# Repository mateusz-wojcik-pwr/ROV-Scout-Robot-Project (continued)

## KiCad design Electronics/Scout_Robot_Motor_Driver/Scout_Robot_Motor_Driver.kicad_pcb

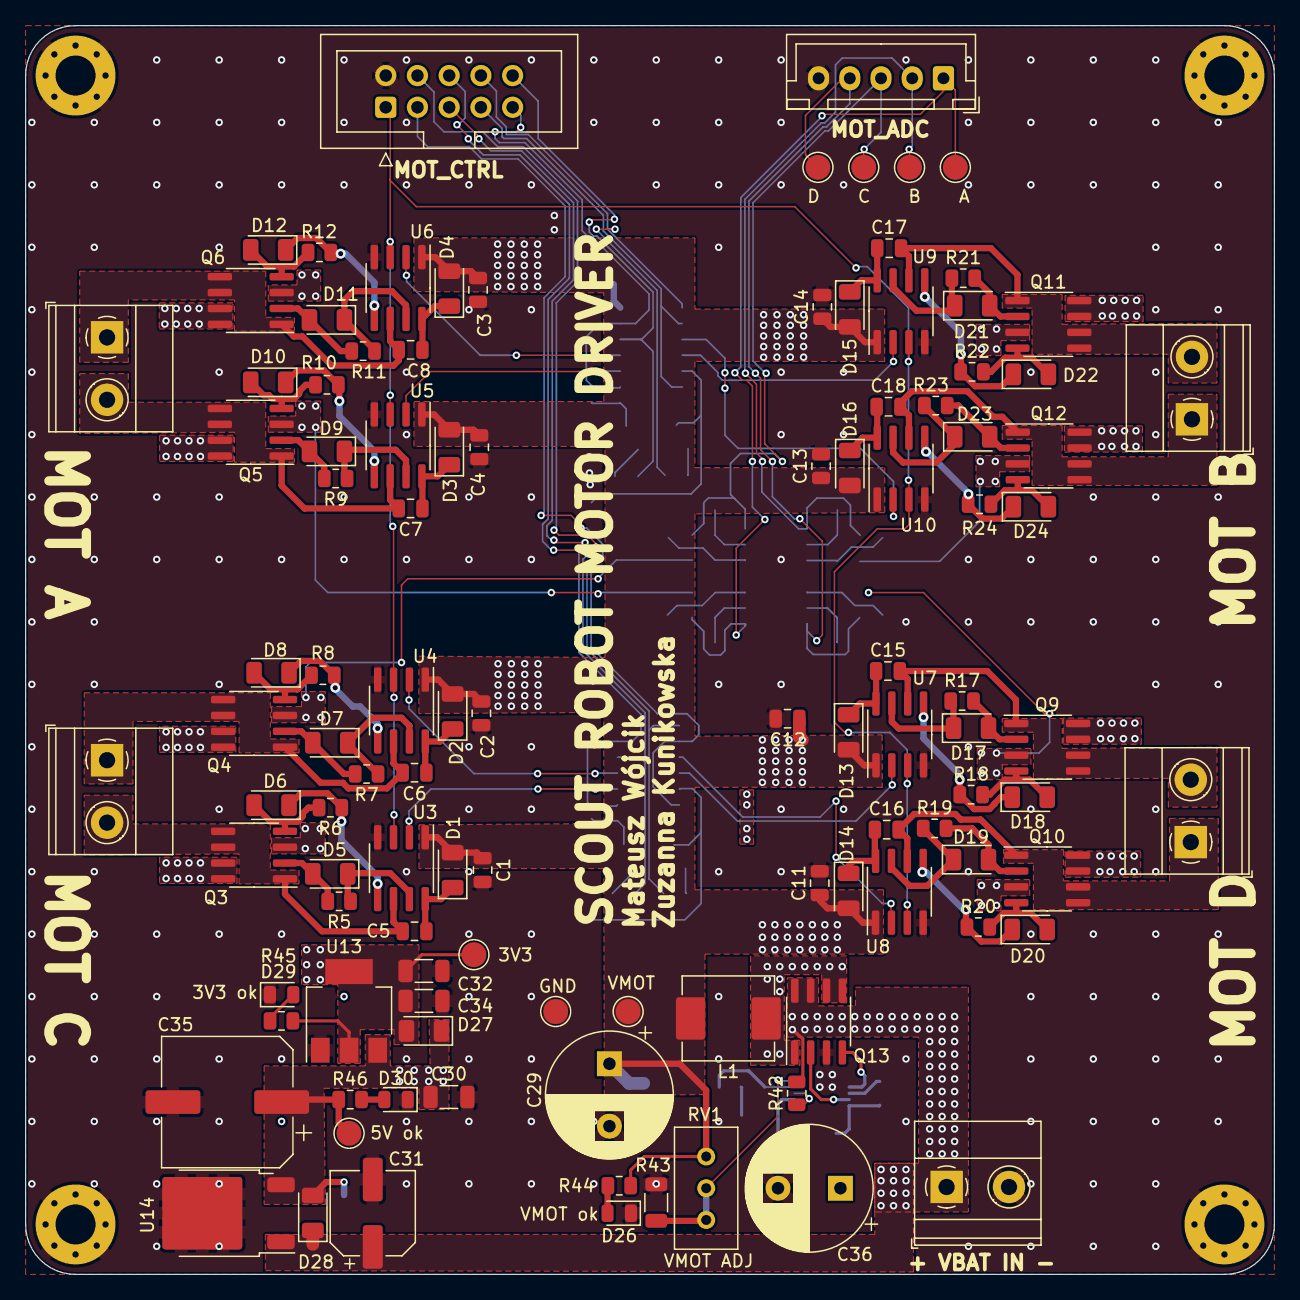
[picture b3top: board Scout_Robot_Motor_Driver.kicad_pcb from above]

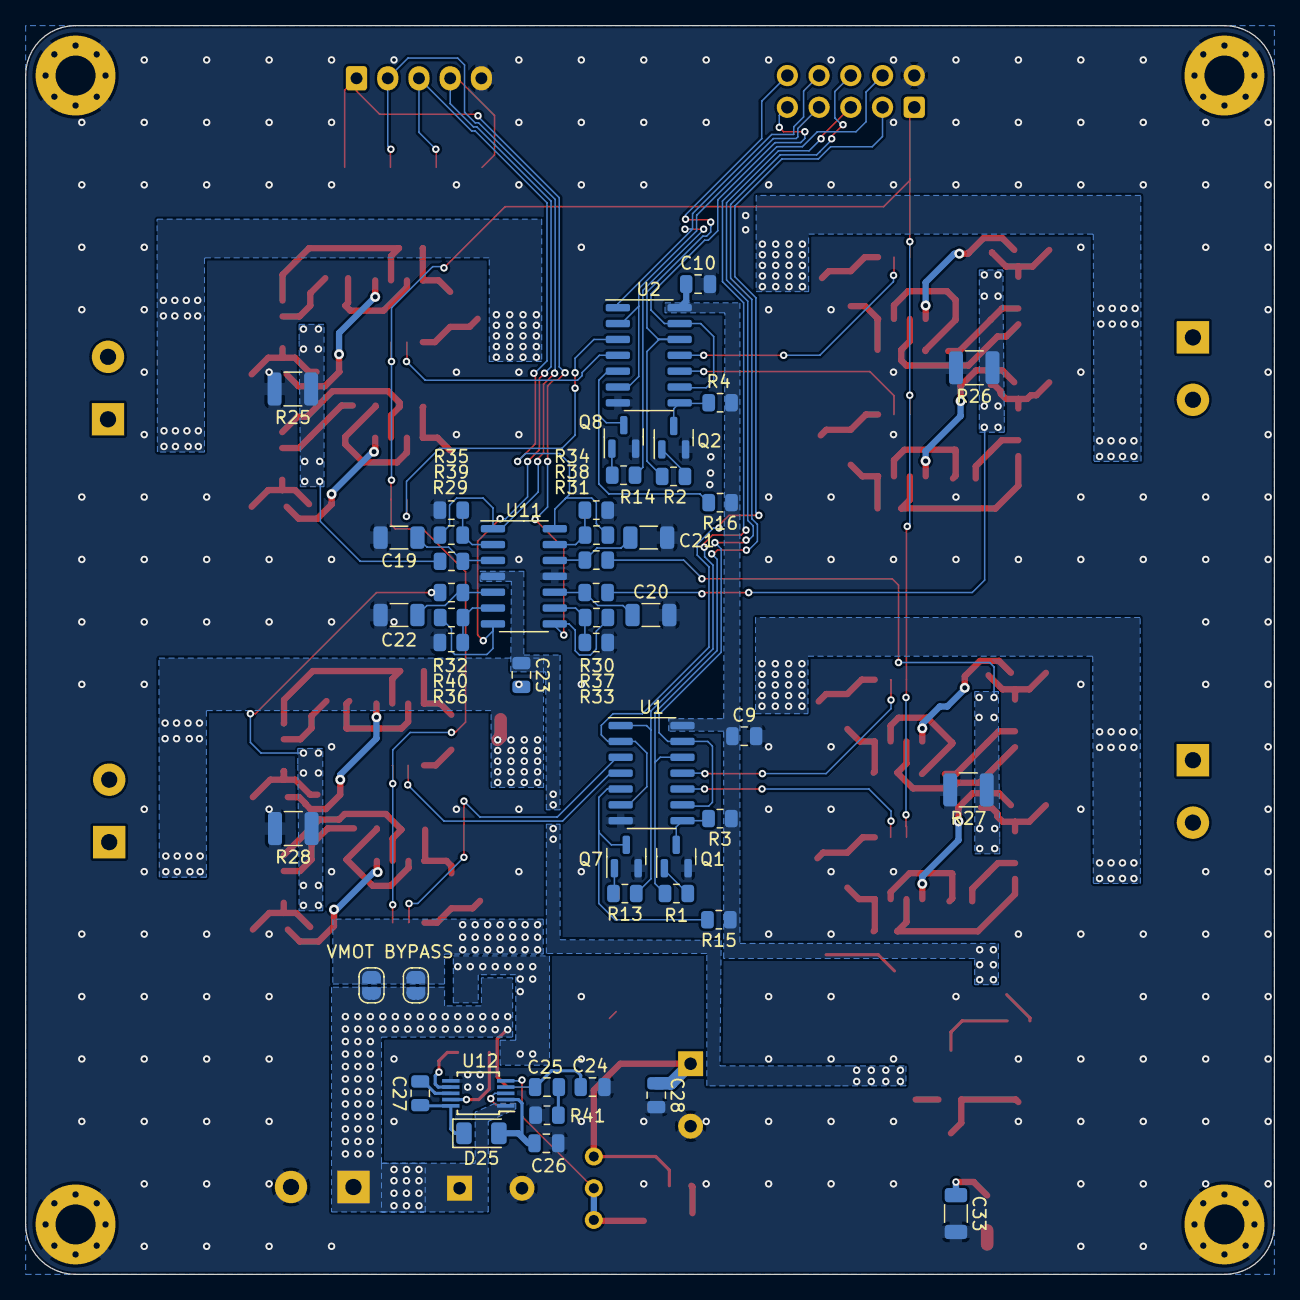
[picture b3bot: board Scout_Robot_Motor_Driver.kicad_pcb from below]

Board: 2 copper layers, 100.0 x 100.0 mm, 162 parts (49 on the bottom side), 107 nets.

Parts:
C1, C2, C3, C4, C5, C6, C7, C8, C9, C10, C11, C12, C13, C14, C15, C16, C17, C18, C23, C25, C26, C27, C28: 100n; C_0805_2012Metric
C19, C20, C21, C22, C30, C32, C33, C34: 1u; C_1206_3216Metric
C24: 100p; C_0805_2012Metric
C29, C36: 470u/25V; CP_Radial_D10.0mm_P5.00mm
C31: 47u/35V; CP_Elec_6.3x5.8
C35: 1m/10V; CP_Elec_10x7.9
D1, D2, D3, D4, D5, D6, D7, D8, D9, D10, D11, D12, D13, D14, D15, D16, D17, D18, D19, D20, D21, D22, D23, D24, D25, D27, D28: D; D_1206_3216Metric
D26: V_MOT_OK; LED_0805_2012Metric
D29: 3V3_OK; LED_0805_2012Metric
D30: 5V_ok; LED_0805_2012Metric
H1, H2, H3, H4: MH; MountingHole_3.2mm_M3_Pad_Via
J1: MOT_A; TerminalBlock_Phoenix_MKDS-1,5-2_1x02_P5.00mm_Horizontal
J2: MOT_B; TerminalBlock_Phoenix_MKDS-1,5-2_1x02_P5.00mm_Horizontal
J3: MOT_C; TerminalBlock_Phoenix_MKDS-1,5-2_1x02_P5.00mm_Horizontal
J4: MOT_D; TerminalBlock_Phoenix_MKDS-1,5-2_1x02_P5.00mm_Horizontal
J5: MOTOR_CONTROL; IDC-Header_2x05_P2.54mm_Vertical
J6: VCC_IN; TerminalBlock_Phoenix_MKDS-1,5-2_1x02_P5.00mm_Horizontal
J7: ADC_CURR_CONN; JST_XH_B5B-XH-A_1x05_P2.50mm_Vertical
JP1, JP2: VMOT_BYPASS; SolderJumper-2_P1.3mm_Open_RoundedPad1.0x1.5mm
L1: 2u2/8A; FERROCORE_HP0630
Q1, Q2, Q7, Q8: Q_NPN_BEC; SOT-23
Q3, Q4, Q5, Q6, Q9, Q10, Q11, Q12, Q13: YJSD12N03A; SOIC-8_3.9x4.9mm_P1.27mm
R1, R2, R13, R14: 22k; R_0805_2012Metric
R3, R4, R15, R16, R44: 1k; R_0805_2012Metric
R5, R6, R7, R8, R9, R10, R11, R12, R17, R18, R19, R20, R21, R22, R23, R24: 10R; R_0805_2012Metric
R25, R26, R27, R28: 50m; R_1210_3225Metric
R29, R30, R31, R32, R33, R34, R35, R36, R41: 4k7; R_0805_2012Metric
R37, R38, R39, R40: 47k; R_0805_2012Metric
R42, R46: 680R; R_0805_2012Metric
R43: 1k5; R_1206_3216Metric
R45: 220R; R_0805_2012Metric
RV1: 22k; Potentiometer_Bourns_3296W_Vertical
TP1, TP3: MOT_A_CURR_TP; TestPoint_Pad_D2.0mm
TP2: MOT_D_CURR_TP; TestPoint_Pad_D2.0mm
TP4: MOT_B_CURR_TP; TestPoint_Pad_D2.0mm
TP5: VD_TP; TestPoint_Pad_D2.0mm
TP6: GND_TP; TestPoint_Pad_D2.0mm
TP7: 3V3_TP; TestPoint_Pad_D2.0mm
TP8: 5V_TP; TestPoint_Pad_D2.0mm
U1, U2: 4081; SOIC-14_3.9x8.7mm_P1.27mm
U3, U4, U5, U6, U7, U8, U9, U10: IR2104; SOIC-8_3.9x4.9mm_P1.27mm
U11: LM324; SOIC-14_3.9x8.7mm_P1.27mm
U12: MIC2168; MSOP-10_3x3mm_P0.5mm
U13: AP1117-33; SOT-223-3_TabPin2
U14: L7805; TO-252-2

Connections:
+3V3: C9.1, C10.1, C32.1, C34.1, D27.2 (A), R3.1, R4.1, R15.1, R16.1, R45.1, TP7.1, U1.14 (VDD), U2.14 (VDD), U13.2 (VO)
+5V: C23.1, C30.1, C33.1, C35.1, D27.1 (K), D28.2 (A), R46.1, TP8.1, U11.4 (V+), U13.3 (VI), U14.3 (OUT)
/H_Bridges/MOT_A_1: C7.2, J1.2, Q5.1 (S1), Q5.5 (D2), Q5.6 (D2), U5.6 (VS)
/H_Bridges/MOT_A_2: C8.2, J1.1, Q6.1 (S1), Q6.5 (D2), Q6.6 (D2), U6.6 (VS)
/H_Bridges/MOT_A_GND: Q5.3 (S2), Q6.3 (S2), R26.1, R30.2
/H_Bridges/MOT_B_1: C17.2, J2.2, Q11.1 (S1), Q11.5 (D2), Q11.6 (D2), U9.6 (VS)
/H_Bridges/MOT_B_2: C18.2, J2.1, Q12.1 (S1), Q12.5 (D2), Q12.6 (D2), U10.6 (VS)
/H_Bridges/MOT_B_GND: Q11.3 (S2), Q12.3 (S2), R25.1, R29.2
/H_Bridges/MOT_C_1: C5.2, J3.2, Q3.1 (S1), Q3.5 (D2), Q3.6 (D2), U3.6 (VS)
/H_Bridges/MOT_C_2: C6.2, J3.1, Q4.1 (S1), Q4.5 (D2), Q4.6 (D2), U4.6 (VS)
/H_Bridges/MOT_C_GND: Q3.3 (S2), Q4.3 (S2), R27.1, R31.2
/H_Bridges/MOT_D_1: C15.2, J4.2, Q9.1 (S1), Q9.5 (D2), Q9.6 (D2), U7.6 (VS)
/H_Bridges/MOT_D_2: C16.2, J4.1, Q10.1 (S1), Q10.5 (D2), Q10.6 (D2), U8.6 (VS)
/H_Bridges/MOT_D_GND: Q9.3 (S2), Q10.3 (S2), R28.1, R32.2
GND: C1.2, C2.2, C3.2, C4.2, C9.2, C10.2, C11.2, C12.2, C13.2, C14.2, C19.2, C20.2, C21.2, C22.2, C23.2, C24.2, C26.2, C28.2, C29.2, C30.2, C31.2, C32.2, C33.2, C34.2, C35.2, C36.2, D26.1 (K), D29.1 (K), D30.1 (K), H1.1, H2.1, H3.1, H4.1, J5.2, J6.2, J7.5, Q1.2 (E), Q2.2 (E), Q7.2 (E), Q8.2 (E), Q13.3 (S2), R25.2, R26.2, R27.2, R28.2, R33.1, R34.1, R35.1, R36.1, R41.1, R43.2, TP6.1, U1.7 (VSS), U2.7 (VSS), U3.4 (COM), U4.4 (COM), U5.4 (COM), U6.4 (COM), U7.4 (COM), U8.4 (COM), U9.4 (COM), U10.4 (COM), U11.11 (V-), U12.6 (GND), U13.1 (GND), U14.2 (GND)
MOT_A_CURR_ADC: J7.1, R37.2, TP1.1, U11.8
MOT_A_DIR: J5.10, R2.1, U2.12
MOT_A_PWM: J5.9, U2.9, U2.13
MOT_B_CURR_ADC: J7.2, R39.2, TP3.1, U11.1
MOT_B_DIR: J5.8, R14.1, U2.1
MOT_B_PWM: J5.7, U2.2, U2.6
MOT_C_CURR_ADC: J7.3, R38.2, TP2.1, U11.14
MOT_C_DIR: J5.6, R1.1, U1.12
MOT_C_PWM: J5.5, U1.9, U1.13
MOT_D_CURR_ADC: J7.4, R40.2, TP4.1, U11.7
MOT_D_DIR: J5.4, R13.1, U1.1
MOT_D_PWM: J5.3, U1.2, U1.6
MOT_EN: J5.1, U3.3 (~SD), U4.3 (~SD), U5.3 (~SD), U6.3 (~SD), U7.3 (~SD), U8.3 (~SD), U9.3 (~SD), U10.3 (~SD)
unnamed: C25.2, R41.2
unnamed: C5.1, D1.1 (K), U3.8 (VB)
unnamed: C6.1, D2.1 (K), U4.8 (VB)
unnamed: C7.1, D3.1 (K), U5.8 (VB)
unnamed: C8.1, D4.1 (K), U6.8 (VB)
unnamed: D5.2 (A), Q3.2 (G1), R5.2
unnamed: D5.1 (K), R5.1, U3.7 (HO)
unnamed: D6.2 (A), Q3.4 (G2), R6.2
unnamed: D6.1 (K), R6.1, U3.5 (LO)
unnamed: D7.2 (A), Q4.2 (G1), R7.2
unnamed: D7.1 (K), R7.1, U4.7 (HO)
unnamed: D8.2 (A), Q4.4 (G2), R8.2
unnamed: D8.1 (K), R8.1, U4.5 (LO)
unnamed: D9.2 (A), Q5.2 (G1), R9.2
unnamed: D9.1 (K), R9.1, U5.7 (HO)
unnamed: D10.2 (A), Q5.4 (G2), R10.2
unnamed: D10.1 (K), R10.1, U5.5 (LO)
unnamed: D11.2 (A), Q6.2 (G1), R11.2
unnamed: D11.1 (K), R11.1, U6.7 (HO)
unnamed: D12.2 (A), Q6.4 (G2), R12.2
unnamed: D12.1 (K), R12.1, U6.5 (LO)
unnamed: C15.1, D13.1 (K), U7.8 (VB)
unnamed: C16.1, D14.1 (K), U8.8 (VB)
unnamed: C17.1, D15.1 (K), U9.8 (VB)
unnamed: C18.1, D16.1 (K), U10.8 (VB)
unnamed: D17.2 (A), Q9.2 (G1), R17.2
unnamed: D17.1 (K), R17.1, U7.7 (HO)
unnamed: D18.2 (A), Q9.4 (G2), R18.2
unnamed: D18.1 (K), R18.1, U7.5 (LO)
unnamed: D19.2 (A), Q10.2 (G1), R19.2
unnamed: D19.1 (K), R19.1, U8.7 (HO)
unnamed: D20.2 (A), Q10.4 (G2), R20.2
unnamed: D20.1 (K), R20.1, U8.5 (LO)
unnamed: D21.2 (A), Q11.2 (G1), R21.2
unnamed: D21.1 (K), R21.1, U9.7 (HO)
unnamed: D22.2 (A), Q11.4 (G2), R22.2
unnamed: D22.1 (K), R22.1, U9.5 (LO)
unnamed: D23.2 (A), Q12.2 (G1), R23.2
unnamed: D23.1 (K), R23.1, U10.7 (HO)
unnamed: D24.2 (A), Q12.4 (G2), R24.2
unnamed: D24.1 (K), R24.1, U10.5 (LO)
unnamed: C26.1, D25.2 (A), U12.2 (VDD)
unnamed: C27.1, D25.1 (K), U12.10 (BST)
unnamed: D26.2 (A), R44.2
unnamed: D29.2 (A), R45.2
unnamed: D30.2 (A), R46.2
unnamed: Q1.1 (B), R1.2
unnamed: Q1.3 (C), R3.2, U1.8
unnamed: Q2.1 (B), R2.2
unnamed: Q2.3 (C), R4.2, U2.8
unnamed: Q7.1 (B), R13.2
unnamed: Q7.3 (C), R15.2, U1.5
unnamed: Q8.1 (B), R14.2
unnamed: Q8.3 (C), R16.2, U2.5
unnamed: Q13.2 (G1), U12.9 (HSD)
unnamed: L1.1, Q13.1 (S1), Q13.5 (D2), Q13.6 (D2)
unnamed: Q13.4 (G2), U12.7 (LSD)
unnamed: U1.10, U3.2 (IN)
unnamed: U1.11, U4.2 (IN)
unnamed: U2.10, U5.2 (IN)
unnamed: U2.11, U6.2 (IN)
unnamed: U1.4, U7.2 (IN)
unnamed: U1.3, U8.2 (IN)
unnamed: U2.4, U9.2 (IN)
unnamed: U2.3, U10.2 (IN)
unnamed: C19.1, R29.1, U11.3 (+)
unnamed: R35.2, R39.1, U11.2 (-)
unnamed: C22.1, R32.1, U11.5 (+)
unnamed: R36.2, R40.1, U11.6 (-)
unnamed: C20.1, R30.1, U11.10 (+)
unnamed: R33.2, R37.1, U11.9 (-)
unnamed: C21.1, R31.1, U11.12 (+)
unnamed: R34.2, R38.1, U11.13 (-)
unnamed: C24.1, C25.1, U12.4 (COMP/EN)
unnamed: R42.1, U12.3 (CS)
unnamed: R43.1, RV1.1, RV1.2, U12.5 (FB)
unnamed: C27.2, U12.8 (VSW)
VCC: C31.1, C36.1, D28.1 (K), J6.1, JP1.1 (A), JP2.1 (A), Q13.7 (D1), Q13.8 (D1), R42.2, U12.1 (VIN), U14.1 (IN)
VD: C1.1, C2.1, C3.1, C4.1, C11.1, C12.1, C13.1, C14.1, C28.1, C29.1, D1.2 (A), D2.2 (A), D3.2 (A), D4.2 (A), D13.2 (A), D14.2 (A), D15.2 (A), D16.2 (A), JP1.2 (B), JP2.2 (B), L1.2, Q3.7 (D1), Q3.8 (D1), Q4.7 (D1), Q4.8 (D1), Q5.7 (D1), Q5.8 (D1), Q6.7 (D1), Q6.8 (D1), Q9.7 (D1), Q9.8 (D1), Q10.7 (D1), Q10.8 (D1), Q11.7 (D1), Q11.8 (D1), Q12.7 (D1), Q12.8 (D1), R44.1, RV1.3, TP5.1, U3.1 (VCC), U4.1 (VCC), U5.1 (VCC), U6.1 (VCC), U7.1 (VCC), U8.1 (VCC), U9.1 (VCC), U10.1 (VCC)

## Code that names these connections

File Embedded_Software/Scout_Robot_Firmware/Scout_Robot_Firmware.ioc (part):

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Mcu.Name=STM32L476R(C-E-G)Tx
Mcu.Package=LQFP64
Mcu.UserName=STM32L476RGTx
PA0.GPIOParameters=GPIO_Label
PA0.GPIO_Label=BAT_CURR_CHRG_ADC
PA0.Signal=ADCx_IN5
PA1.GPIOParameters=GPIO_Label
PA1.GPIO_Label=US_SENS_B_TRIG
PA1.Signal=GPIO_Output
PA10.GPIOParameters=GPIO_Label
PA10.GPIO_Label=US_SENS_C_ECHO
PA10.Signal=S_TIM1_CH3
PA11.GPIOParameters=GPIO_Label
PA11.GPIO_Label=CHRG_EN
PA11.Signal=GPIO_Output
PA12.GPIOParameters=GPIO_Label
PA12.GPIO_Label=PWR_LEDS_EN
PA12.Signal=GPIO_Output
PA13\ (JTMS-SWDIO).GPIOParameters=GPIO_Label
PA13\ (JTMS-SWDIO).GPIO_Label=TMS
PA13\ (JTMS-SWDIO).Mode=Serial_Wire
PA13\ (JTMS-SWDIO).Signal=SYS_JTMS-SWDIO
PA14\ (JTCK-SWCLK).GPIOParameters=GPIO_Label
PA14\ (JTCK-SWCLK).GPIO_Label=TCK
PA14\ (JTCK-SWCLK).Mode=Serial_Wire
PA14\ (JTCK-SWCLK).Signal=SYS_JTCK-SWCLK
PA15\ (JTDI).GPIOParameters=GPIO_Label
PA15\ (JTDI).GPIO_Label=MOT_D_DIR
PA15\ (JTDI).Signal=GPIO_Output
PA2.GPIOParameters=GPIO_Speed,GPIO_PuPd,GPIO_Label,GPIO_Mode
PA2.GPIO_Label=USART_TX
PA2.GPIO_Mode=GPIO_MODE_AF_PP
PA2.GPIO_PuPd=GPIO_NOPULL
PA2.GPIO_Speed=GPIO_SPEED_FREQ_VERY_HIGH
PA2.Mode=Asynchronous
PA2.Signal=USART2_TX
PA3.GPIOParameters=GPIO_Speed,GPIO_PuPd,GPIO_Label,GPIO_Mode
PA3.GPIO_Label=USART_RX
PA3.GPIO_Mode=GPIO_MODE_AF_PP
PA3.GPIO_PuPd=GPIO_NOPULL
PA3.GPIO_Speed=GPIO_SPEED_FREQ_VERY_HIGH
PA3.Mode=Asynchronous
PA3.Signal=USART2_RX
PA4.GPIOParameters=GPIO_Label
PA4.GPIO_Label=US_SENS_C_TRIG
PA4.Signal=GPIO_Output
PA5.GPIOParameters=GPIO_Speed,GPIO_PuPd,GPIO_Label,GPIO_ModeDefaultOutputPP
PA5.GPIO_Label=LD2 [green Led]
PA5.GPIO_ModeDefaultOutputPP=GPIO_MODE_OUTPUT_PP
PA5.GPIO_PuPd=GPIO_NOPULL
PA5.GPIO_Speed=GPIO_SPEED_FREQ_LOW
PA5.Signal=GPIO_Output
PA6.GPIOParameters=GPIO_Label
PA6.GPIO_Label=BAT_CURR_DISCH_ADC
PA6.Signal=ADCx_IN11
PA7.GPIOParameters=GPIO_Label
PA7.GPIO_Label=V_BAT_ADC
PA7.Signal=ADCx_IN12
PA8.GPIOParameters=GPIO_Label
PA8.GPIO_Label=US_SENS_A_ECHO
PA8.Signal=S_TIM1_CH1
PA9.GPIOParameters=GPIO_Label
PA9.GPIO_Label=US_SENS_B_ECHO
PA9.Signal=S_TIM1_CH2
PB0.GPIOParameters=GPIO_Label
PB0.GPIO_Label=NRF_CSN
PB0.Signal=GPIO_Output
PB1.GPIOParameters=GPIO_Label
PB1.GPIO_Label=NRF_CE
PB1.Signal=GPIO_Output
PB10.Mode=I2C
PB10.Signal=I2C2_SCL
PB11.Mode=I2C
PB11.Signal=I2C2_SDA
PB12.GPIOParameters=GPIO_Label
PB12.GPIO_Label=US_SENS_A_TRIG
PB12.Signal=GPIO_Output
PB13.Mode=Full_Duplex_Master
PB13.Signal=SPI2_SCK
PB14.Mode=Full_Duplex_Master
PB14.Signal=SPI2_MISO
PB15.Mode=Full_Duplex_Master
PB15.Signal=SPI2_MOSI
PB2.GPIOParameters=GPIO_Label
PB2.GPIO_Label=NRF_IRQ
PB2.Signal=GPXTI2
PB3\ (JTDO-TRACESWO).GPIOParameters=GPIO_Label
PB3\ (JTDO-TRACESWO).GPIO_Label=SWO
PB3\ (JTDO-TRACESWO).Signal=SYS_JTDO-SWO
PB5.GPIOParameters=GPIO_Label
PB5.GPIO_Label=WSLED_DIN
PB5.Signal=GPIO_Output
PB6.Mode=Asynchronous
PB6.Signal=USART1_TX
PB7.Mode=Asynchronous
PB7.Signal=USART1_RX
PB8.Mode=I2C
PB8.Signal=I2C1_SCL
PB9.Mode=I2C
PB9.Signal=I2C1_SDA
PC0.GPIOParameters=GPIO_Label
PC0.GPIO_Label=MOT_A_CURR_ADC
PC0.Signal=ADCx_IN1
PC1.GPIOParameters=GPIO_Label
PC1.GPIO_Label=MOT_B_CURR_ADC
PC1.Signal=ADCx_IN2
PC10.GPIOParameters=GPIO_Label
PC10.GPIO_Label=MOT_C_DIR
PC10.Signal=GPIO_Output
PC11.GPIOParameters=GPIO_Label
PC11.GPIO_Label=MOT_B_DIR
PC11.Signal=GPIO_Output
PC12.GPIOParameters=GPIO_Label
PC12.GPIO_Label=MOT_A_DIR
PC12.Signal=GPIO_Output
PC13.GPIOParameters=GPIO_PuPd,GPIO_Label,GPIO_ModeDefaultEXTI
PC13.GPIO_Label=B1 [Blue PushButton]
PC13.GPIO_ModeDefaultEXTI=GPIO_MODE_IT_FALLING
PC13.GPIO_PuPd=GPIO_NOPULL
PC13.Signal=GPXTI13
PC14-OSC32_IN\ (PC14).Mode=LSE-External-Oscillator
PC14-OSC32_IN\ (PC14).Signal=RCC_OSC32_IN
PC15-OSC32_OUT\ (PC15).Mode=LSE-External-Oscillator
PC15-OSC32_OUT\ (PC15).Signal=RCC_OSC32_OUT
PC2.GPIOParameters=GPIO_Label
PC2.GPIO_Label=MOT_C_CURR_ADC
PC2.Signal=ADCx_IN3
PC3.GPIOParameters=GPIO_Label
PC3.GPIO_Label=MOT_D_CURR_ADC
PC3.Signal=ADCx_IN4
PC4.GPIOParameters=GPIO_Label
PC4.GPIO_Label=LIGHT_SENS_ADC
PC4.Signal=ADCx_IN13
PC5.GPIOParameters=GPIO_Label
PC5.GPIO_Label=V_CHRG_ADC
PC5.Signal=ADCx_IN14
PC6.GPIOParameters=GPIO_Label
PC6.GPIO_Label=MOT_A_PWM
PC6.Signal=S_TIM3_CH1
PC7.GPIOParameters=GPIO_Label
PC7.GPIO_Label=MOT_B_PWM
PC7.Signal=S_TIM3_CH2
PC8.GPIOParameters=GPIO_Label
PC8.GPIO_Label=MOT_C_PWM
PC8.Signal=S_TIM3_CH3
PC9.GPIOParameters=GPIO_Label
PC9.GPIO_Label=MOT_D_PWM
PC9.Signal=S_TIM3_CH4
PD2.GPIOParameters=GPIO_Label
PD2.GPIO_Label=MOT_EN
PD2.Signal=GPIO_Output
PH0-OSC_IN\ (PH0).Mode=HSE-External-Oscillator
PH0-OSC_IN\ (PH0).Signal=RCC_OSC_IN
PH1-OSC_OUT\ (PH1).Mode=HSE-External-Oscillator
PH1-OSC_OUT\ (PH1).Signal=RCC_OSC_OUT
RCC.HSE_VALUE=8000000
RCC.SYSCLKFreq_VALUE=80000000
RCC.SYSCLKSource=RCC_SYSCLKSOURCE_PLLCLK
board=NUCLEO-L476RG
boardIOC=true

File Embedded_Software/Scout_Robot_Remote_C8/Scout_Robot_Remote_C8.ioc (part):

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Mcu.Name=STM32F103C(8-B)Tx
Mcu.Package=LQFP48
Mcu.UserName=STM32F103C8Tx
PA0-WKUP.GPIOParameters=GPIO_Label
PA0-WKUP.GPIO_Label=JS_AX_ADC
PA0-WKUP.Signal=ADCx_IN0
PA1.GPIOParameters=GPIO_Label
PA1.GPIO_Label=JS_AY_ADC
PA1.Signal=ADCx_IN1
PA10.Mode=Asynchronous
PA10.Signal=USART1_RX
PA12.GPIOParameters=PinState,GPIO_Label
PA12.GPIO_Label=NRF_CSN
PA12.PinState=GPIO_PIN_SET
PA12.Signal=GPIO_Output
PA2.GPIOParameters=GPIO_Label
PA2.GPIO_Label=JS_BX_ADC
PA2.Signal=ADCx_IN2
PA3.GPIOParameters=GPIO_Label
PA3.GPIO_Label=JS_BX_ADC
PA3.Signal=ADCx_IN3
PA4.GPIOParameters=GPIO_Label
PA4.GPIO_Label=VBAT_ADC
PA4.Signal=ADCx_IN4
PA5.GPIOParameters=GPIO_Label
PA5.GPIO_Label=POT_ADC
PA5.Signal=ADCx_IN5
PA7.GPIOParameters=GPIO_Label
PA7.GPIO_Label=LED1
PA7.Signal=GPIO_Output
PA8.GPIOParameters=GPIO_Label
PA8.GPIO_Label=LCD_CS
PA8.Signal=GPIO_Output
PA9.Mode=Asynchronous
PA9.Signal=USART1_TX
PB0.GPIOParameters=GPIO_Label
PB0.GPIO_Label=LED2
PB0.Signal=GPIO_Output
PB1.GPIOParameters=GPIO_Label
PB1.GPIO_Label=BT3
PB1.Signal=GPIO_Input
PB10.GPIOParameters=GPIO_Label
PB10.GPIO_Label=BT2
PB10.Signal=GPIO_Input
PB11.GPIOParameters=GPIO_Label
PB11.GPIO_Label=BT1
PB11.Signal=GPIO_Input
PB12.GPIOParameters=GPIO_Label
PB12.GPIO_Label=LCD_LED
PB12.Signal=GPIO_Output
PB13.Mode=Full_Duplex_Master
PB13.Signal=SPI2_SCK
PB14.Mode=Full_Duplex_Master
PB14.Signal=SPI2_MISO
PB15.Mode=Full_Duplex_Master
PB15.Signal=SPI2_MOSI
PB6.GPIOParameters=GPIO_Label
PB6.GPIO_Label=NRF_IRQ
PB6.Signal=GPXTI6
PB7.GPIOParameters=PinState,GPIO_Label
PB7.GPIO_Label=NRF_CE
PB7.PinState=GPIO_PIN_SET
PB7.Signal=GPIO_Output
PC13-TAMPER-RTC.GPIOParameters=GPIO_Label
PC13-TAMPER-RTC.GPIO_Label=JS_B_SW
PC13-TAMPER-RTC.Signal=GPIO_Input
PC14-OSC32_IN.GPIOParameters=GPIO_Label
PC14-OSC32_IN.GPIO_Label=JS_A_SW
PC14-OSC32_IN.Signal=GPIO_Input
PD0-OSC_IN.Mode=HSE-External-Oscillator
PD0-OSC_IN.Signal=RCC_OSC_IN
PD1-OSC_OUT.Mode=HSE-External-Oscillator
PD1-OSC_OUT.Signal=RCC_OSC_OUT
RCC.SYSCLKFreq_VALUE=72000000
RCC.SYSCLKSource=RCC_SYSCLKSOURCE_PLLCLK
board=custom

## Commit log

2023-04-26 Import progress from private repo, add basic structure
2023-04-26 Add necessary kicad libraries
2023-04-26 Update gitignore file: do not track stm32cubeide metadata folder and debug folders
2023-04-26 Remove debug folders from embedded software
2023-04-26 Add basic project descritpion in readme
